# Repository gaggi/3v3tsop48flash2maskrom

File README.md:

# 3v3-tsop48-flash2maskrom
A simple PCB for connecting a cheap and easy available 3v3 TSOP48 Flash Chip (eg. 29AL032) to an SNES Cart in place of the standard 36Pin Maskrom.

For prelashed Chips you can simply close R1 and R2 with solder Blobs or small 0805 Type resistors (preferably 4k7 Ohms or lower) and connect #BYTE to 3v3.

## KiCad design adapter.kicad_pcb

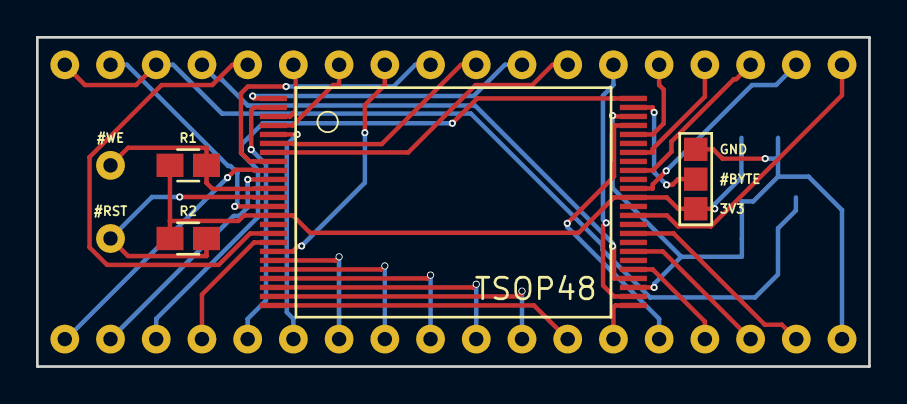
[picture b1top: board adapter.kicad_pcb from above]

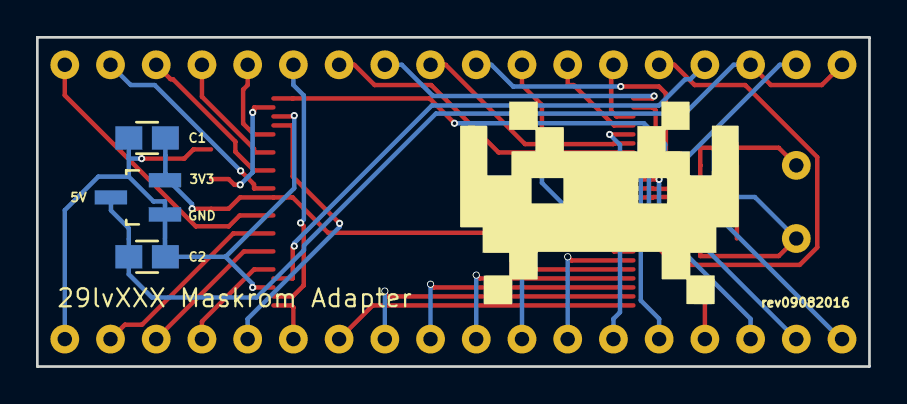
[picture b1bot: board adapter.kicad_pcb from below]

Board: 2 copper layers, 46.2 x 18.3 mm, 10 parts (3 on the bottom side), 39 nets.

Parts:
C1, C2: 10nF; R_0805_HandSoldering
P1: CONN_01X03; 3pin_SMD_SolderJumper
PAD1, PAD2: SolderWirePad_single_0-8mmDrill
R1, R2: 4k7; R_0805_HandSoldering
U1: TSOP48; TSOP-48
U2: LD1117-3.3; SOT-23_Handsoldering
U3: SNES_Mask_ROM; DIP-40_W15.24mm

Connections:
+3V3: C1.2, P1.1, R1.1, R2.1, U1.14, U1.37, U2.2
+5V: C2.2, U2.3, U3.34, U3.36
/A1: U1.25, U3.13
/A2: U1.24, U3.12
/A3: U1.23, U3.11
/A4: U1.22, U3.10
/A5: U1.21, U3.9
/A6: U1.20, U3.8
/A7: U1.19, U3.7
/A8: U1.18, U3.29
/A9: U1.8, U3.28
/A10: U1.7, U3.25
/A11: U1.6, U3.27
/A12: U1.5, U3.6
/A13: U1.4, U3.30
/A14: U1.3, U3.31
/A15: U1.2, U3.5
/A16: U1.1, U3.26
/A17: U1.48, U3.3
/A18: U1.17, U3.4
/A19: U1.16, U3.32
/A20: U1.9, U3.1
/A21: U1.10, U3.2
/A22: U1.13, U3.35
/BYTE: P1.2, U1.47
/CE: U1.26, U3.24
/D0: U1.29, U3.15
/D1: U1.31, U3.16
/D2: U1.33, U3.17
/D3: U1.35, U3.19
/D4: U1.38, U3.20
/D5: U1.40, U3.21
/D6: U1.42, U3.22
/D7: U1.44, U3.23
/OE: U1.28, U3.33
/RST: PAD2.1, R2.2, U1.12
/WE: PAD1.1, R1.2, U1.11
GND: C1.1, C2.1, P1.3, U1.27, U1.46, U2.1, U3.18
unnamed: U1.45, U3.14

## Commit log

2016-08-09 :tada: Added .gitattributes & .gitignore files
2016-08-09 Initial Release
2016-08-10 Routed PCB
